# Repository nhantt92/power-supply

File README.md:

# power-supply
power-supply: buck, boots, pull-push, flyback, switching....

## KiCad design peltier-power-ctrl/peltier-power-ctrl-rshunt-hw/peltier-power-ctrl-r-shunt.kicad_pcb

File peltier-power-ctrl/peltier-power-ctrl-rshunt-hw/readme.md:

#DC-DC-converter using STM8

##Nguyên lý

- Mạch điều khiển công suất sò nóng lạnh

-- Điều khiển theo nhiệt độ

-- Điều khiển công suất ngõ ra

-- Mạch sử dụng VĐK STM8 đo dòng, đo áp, đo nhiệt độ điều khiển công suất ngõ ra

-- Nút mode chọn 3 chế độ: hiển thị dòng điện, điện áp, nhiệt độ.

-- Nhấn nút mode 3s vào chế độ setup, nhấp up, down chọn chế độ: set nhiệt độ, set dòng điện, nhấn mode vào chế độ đó, nhấn up down để tăng giảm từng đơn vị.

##Design

###_schematic_

###_pcb_

###_3d_

##Caculator

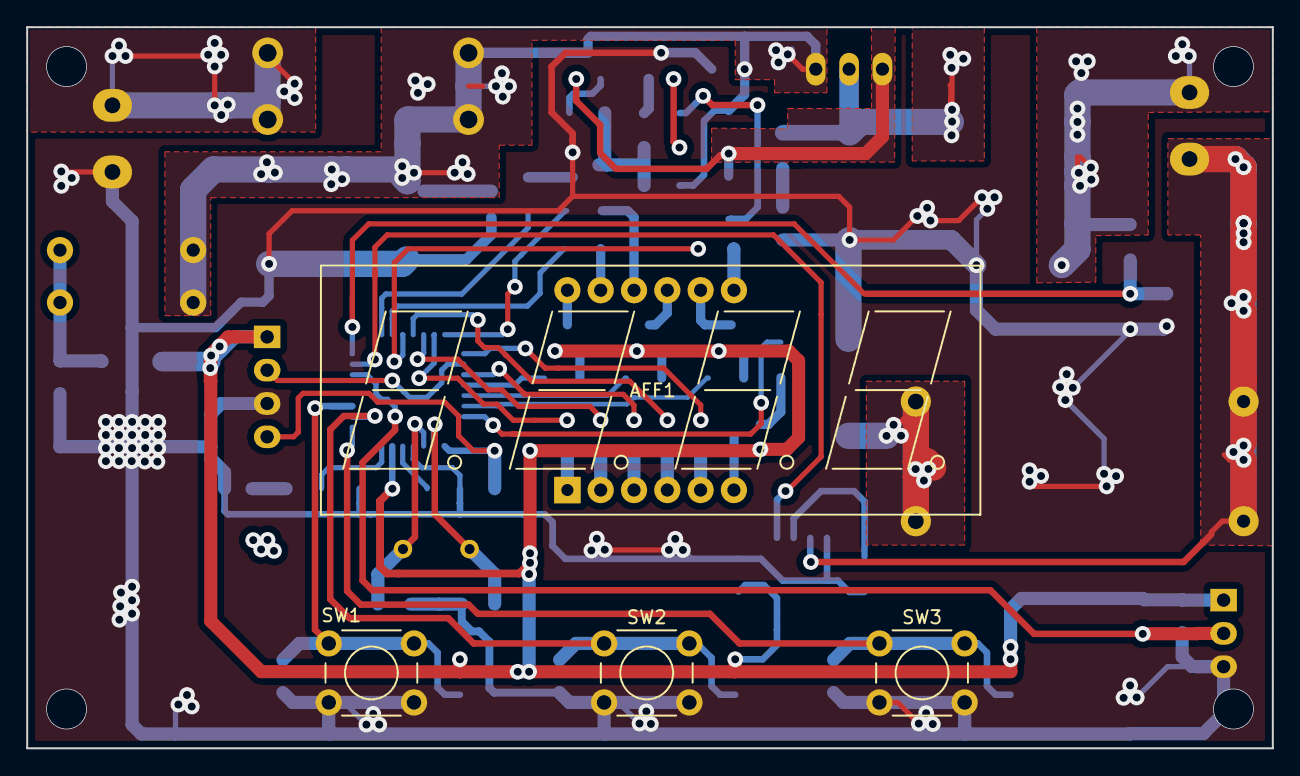
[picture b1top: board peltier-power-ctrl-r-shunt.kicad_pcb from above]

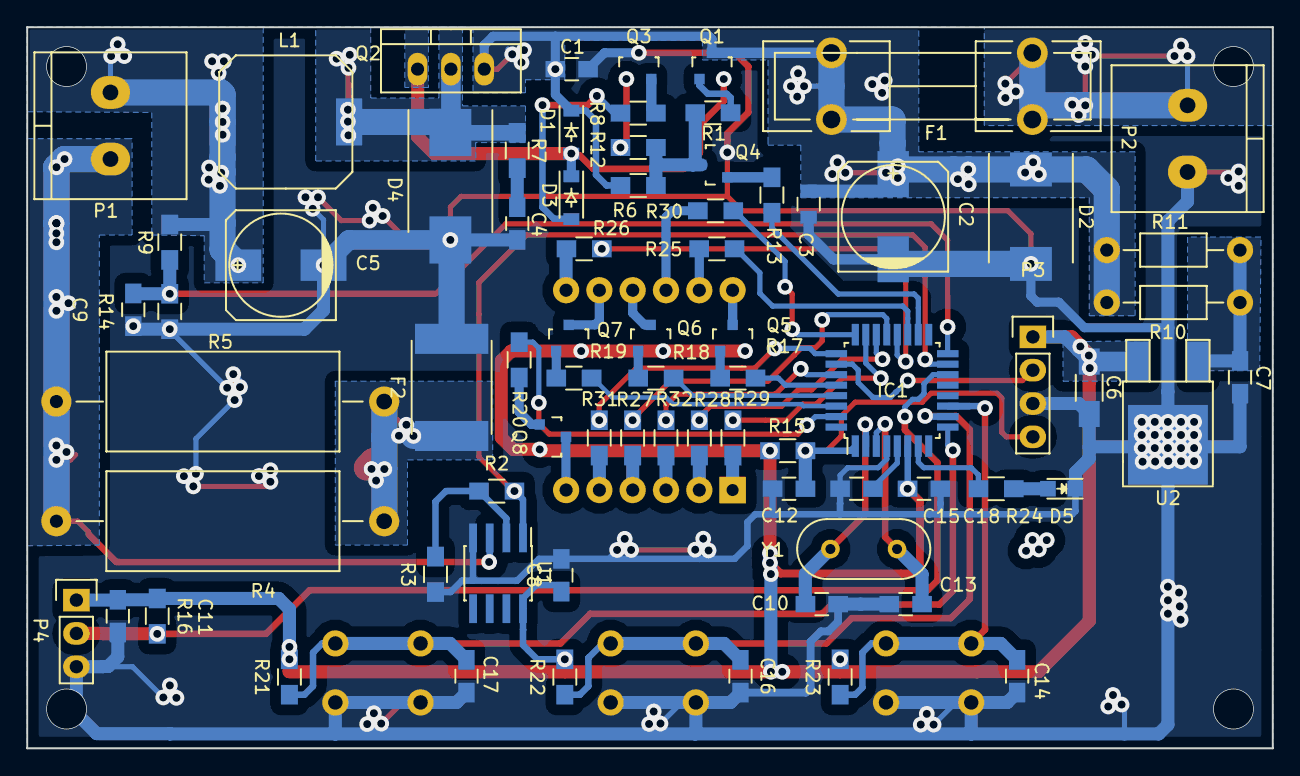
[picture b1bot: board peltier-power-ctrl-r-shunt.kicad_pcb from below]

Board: 2 copper layers, 95.0 x 55.0 mm, 78 parts (74 on the bottom side), 60 nets.

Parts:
AFF1: CA56-12; Cx56-12
C1, C7, C8, C11, C12, C14, C16, C17, C18: 100nF; C_0805_HandSoldering
C2, C5: 470uF; c_elec_8x10.5
C3: 100nF; C_0805
C4, C9: 220p; C_0805_HandSoldering
C6: 10uF; C_1206_HandSoldering
C10, C13: 22p; C_0805_HandSoldering
C15: 0.1uF; C_0805_HandSoldering
D1, D3: 12V; SOD-123
D2: SMAJ36; DO-214AB
D4: SS34; DO-214AB_Handsoldering
D5: LED; LED_0805
F1: FUSE; Fuseholder5x20_horiz_open_lateral_Type-II
F2: FUSE; Fuse_SMD2920
IC1: STM8S003K3T; LQFP-32_7x7mm_Pitch0.8mm
L1: INDUCTOR; self_cms_we-tpc_XL
P1, P2: CONN_01X02; TerminalBlock_Pheonix_PT-5.08mm_2pol
P3: CONN_01X04; Pin_Header_Straight_1x04
P4: CONN_01X03; Pin_Header_Straight_1x03
Q1, Q4: 2SC1815; SOT-23
Q2: Q_PMOS_GSD; TO-220_Neutral123_Vertical
Q3, Q5, Q6, Q7, Q8: 2SA1015; SOT-23
R1, R12, R13, R14, R17, R18, R19, R20: 2.2k; R_0805_HandSoldering
R2, R3, R9, R15, R21, R22, R23: 10k; R_0805_HandSoldering
R4, R5: R; Resistor_Horizontal_RM25mm
R6: 4.7k; R_0805_HandSoldering
R7: 10; R_0805_HandSoldering
R8: 100; R_0805_HandSoldering
R10, R11: R; Resistor_Horizontal_RM10mm
R16: 4.7K; R_0805_HandSoldering
R24: 1k; R_0805_HandSoldering
R25, R26, R27, R28, R29, R30, R31, R32: 220; R_0805_HandSoldering
SW1, SW2, SW3: SW_PUSH; SW_PUSH_6mm
U1: LM358; SOIC-8_3.9x4.9mm_Pitch1.27mm
U2: LM7805CT; TO-252-2Lead
Y1: Crystal; HC-49V

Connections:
+5V: C6.1, C8.1, C11.1, C18.1, IC1.6, P3.1, P4.1, Q5.2, Q6.2, Q7.2, Q8.2, R15.2, R16.2, R21.2, R22.2, R23.2, U1.8, U2.3
+24V: C1.2, C2.1, C3.1, D1.1, D2.1, F1.2, Q1.3, Q2.3, R6.2, R10.2, R11.2
/A: IC1.19, R25.1
/B: IC1.20, R26.1
/C: IC1.21, R27.1
/D: IC1.22, R28.1
/DP: IC1.27, R32.1
/E: IC1.23, R29.1
/F: IC1.24, R30.1
/G: IC1.25, R31.1
/I_FB: IC1.15, R2.2, U1.1
/L1: IC1.28, R17.1
/L2: IC1.29, R18.1
/L3: IC1.30, R19.1
/L4: IC1.31, R20.1
/NRST: C12.1, IC1.1, P3.4, R15.1
/PWM: IC1.18, R13.2
/SWIM: IC1.26, P3.2
/V_FB: C9.1, IC1.16, R9.2, R14.1
/down: C17.2, IC1.9, R21.1, SW3.1
/led_stt: IC1.7, R24.1
/mode: C14.2, IC1.11, R23.1, SW1.1
/tmp: IC1.14, P4.2, R16.1
/up: C16.2, IC1.10, R22.1, SW2.1
GND: C1.1, C2.2, C3.2, C4.2, C5.2, C6.2, C7.2, C8.2, C9.2, C10.1, C11.2, C12.2, C13.1, C14.1, C15.2, C16.1, C17.1, C18.2, D2.2, D4.2, D5.1, F2.2, IC1.4, P2.1, P3.3, P4.3, Q3.3, Q4.2, R3.1, R14.2, SW1.2, SW2.2, SW3.2, U1.4, U2.2
unnamed: AFF1.1, R29.2
unnamed: AFF1.2, R28.2
unnamed: AFF1.3, R32.2
unnamed: AFF1.4, R27.2
unnamed: AFF1.5, R31.2
unnamed: AFF1.6, Q8.3
unnamed: AFF1.7, R26.2
unnamed: AFF1.8, Q7.3
unnamed: AFF1.9, Q6.3
unnamed: AFF1.10, R30.2
unnamed: AFF1.11, R25.2
unnamed: AFF1.12, Q5.3
unnamed: C4.1, R7.2
unnamed: C7.1, R10.1, R11.1, U2.1
unnamed: C10.2, IC1.2, Y1.2
unnamed: C13.2, IC1.3, Y1.1
unnamed: C15.1, IC1.5
unnamed: D1.2, D3.1, Q1.2, Q2.1
unnamed: D3.2, R8.1
unnamed: D4.1, L1.1, Q2.2, R7.1
unnamed: D5.2, R24.2
unnamed: F1.1, P2.2
unnamed: F2.1, R4.2, R5.2
unnamed: P1.2, R4.1, R5.1, U1.3
unnamed: Q1.1, R1.1
unnamed: Q3.1, R12.1
unnamed: Q3.2, R8.2
unnamed: Q4.1, R13.1
unnamed: Q4.3, R1.2, R6.1, R12.2
unnamed: Q5.1, R17.2
unnamed: Q6.1, R18.2
unnamed: Q7.1, R19.2
unnamed: Q8.1, R20.2
unnamed: R2.1, R3.2, U1.2
Vout: C5.1, L1.2, P1.1, R9.1

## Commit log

2016-09-09 init project
2016-09-17 pcb voltage-dc-dc-buck-stm8
2016-09-17 modified readme voltage-buck
2016-09-21 add pcb current-source
2016-10-12 add project pcb peltier-ctrl-power
